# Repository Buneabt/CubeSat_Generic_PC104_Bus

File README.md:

# A Generic CubeSat Bus

This project creates a generic CubeSat PC104 bus with stack through headers implemented. If desired these headers can be replaced with a non-stack through version as denoted in the project files of this repository. This project also **does not** contain a premade Gerber or POS files for component mapping and need to be created by the user. 

This project was originally adapted from a LibreCube repository which created the base for this outline. 

## This board has currently been used to develop the following: <br>
**GWU-Sat**: Digipeater <br>
**GWU-Sat**: IMU Mounting for PiMAGGRYO <br>
**GWU-Sat**: Endurosat Transceiver RS-485 <-> UART converter<br>

## Images

<div align="center">
  
*Schematic*

<div>

<div align="center">
  
*PCB*

<div>

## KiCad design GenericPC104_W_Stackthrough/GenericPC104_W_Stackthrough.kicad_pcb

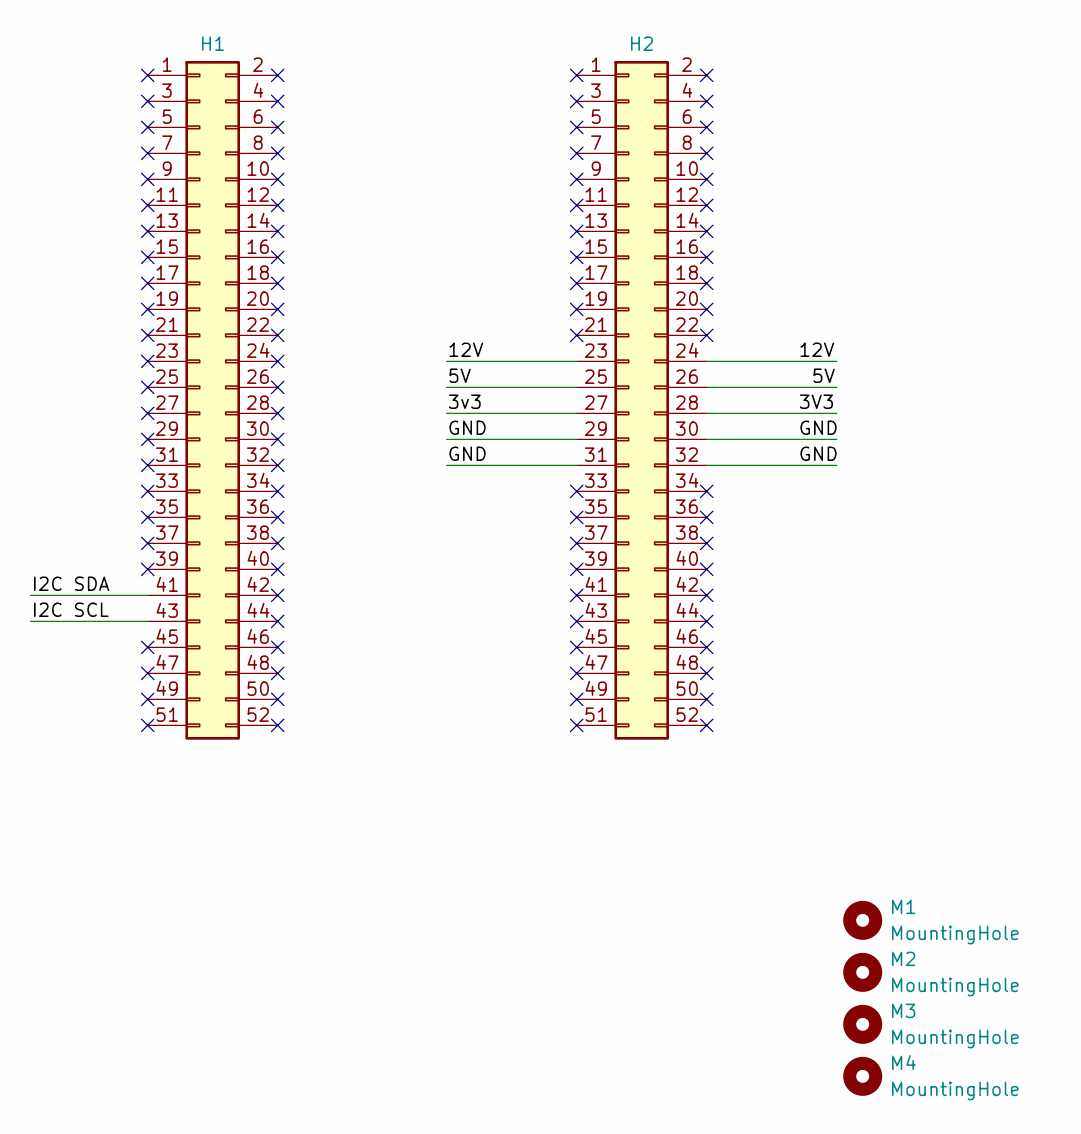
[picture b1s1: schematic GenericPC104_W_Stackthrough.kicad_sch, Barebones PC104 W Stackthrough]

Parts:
H1, H2: PC/104 Connector; ESQ-126-Y-X-D
M1, M2, M3, M4: MountingHole; MountingHole_3.2mm_M3_Pad

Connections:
/3V3: H2.28
/3v3: H2.27
/5V: H2.25, H2.26
/12V: H2.23, H2.24
/GND: H2.29, H2.30, H2.31, H2.32
/I2C SCL: H1.43
/I2C SDA: H1.41

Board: 6 copper layers, 6 parts (0 on the bottom side), 3 nets, no tracks yet.
